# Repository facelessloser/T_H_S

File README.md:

# T_H_S

https://facelesstech.files.wordpress.com/2015/07/main_ths2.jpg

Low cost open source heart rate and body temperature monitor

Blog post can be found here

https://facelesstech.wordpress.com/2015/07/31/temp_heart_sensor/

Hackaday.io post can be found here 

https://hackaday.io/project/4910-ths

Video can be found here 

https://youtu.be/P-qDKN8uHOM

https://www.youtube.com/watch?v=heoFKFPPkZ0

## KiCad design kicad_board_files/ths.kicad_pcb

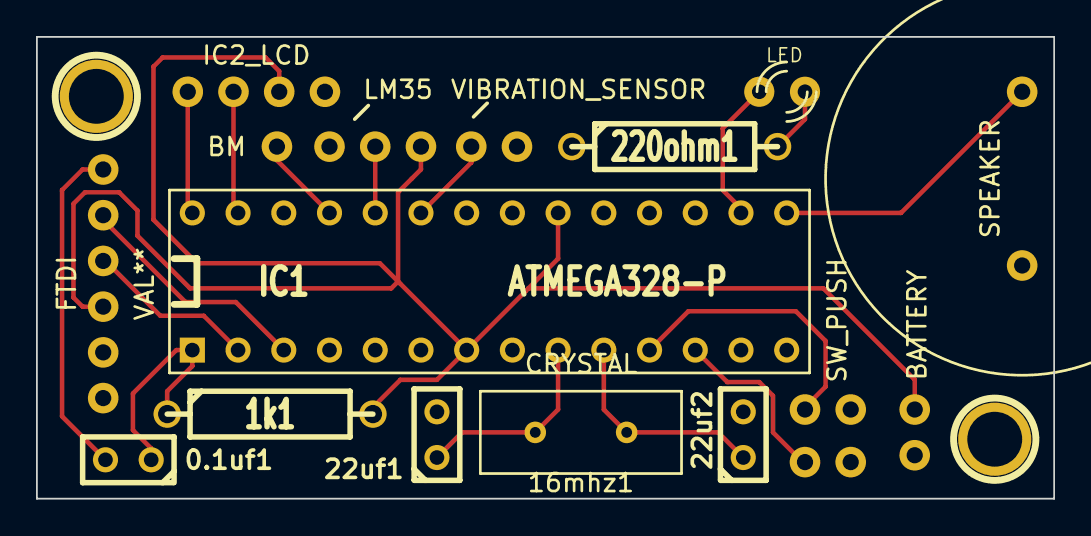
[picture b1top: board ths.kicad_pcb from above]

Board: 2 copper layers, 56.5 x 25.7 mm, 20 parts (0 on the bottom side), 15 nets.

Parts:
0.1uf1, 22uf1, 22uf2: C; C1
1PIN, 1PIN#2: P***; 1pin
1k1, 220ohm1: R; R4-5
16mhz1: CRYSTAL; Crystal_custom
BT1: BATTERY; battery_custom
D1: LED; LED_custom
FTDI: VAL**; FTDI
IC1: ATMEGA328-P; atmega328_socket
IC2_LCD1: IC2_LCD; LCD_I2C_Custom
SP1: SPEAKER; speaker_custom
SW1, SW2: SW_PUSH; push_button_custom
U1: LM35
U2: VIBRATION_SENSOR; vibration_sensor
U3: BM; battery_monitor
VAL: OSH_final_silks_back

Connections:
GND: 22uf1.2, 22uf2.2, 220ohm1.1, BT1.2, IC1.8, IC1.22, IC2_LCD1.1, SP1.1, SW1.1, SW2.1, U1.3, U2.1
unnamed: D1.1, IC1.16
unnamed: 220ohm1.2, D1.2
unnamed: IC1.15, SP1.2
unnamed: IC1.11, SW2.2
unnamed: IC1.23, U2.2
unnamed: IC1.25, U3.1
unnamed: IC1.12, SW1.2
unnamed: IC1.24, U1.2
unnamed: 16mhz1.1, 22uf2.1, IC1.10
unnamed: IC1.27, IC2_LCD1.3
unnamed: IC1.28, IC2_LCD1.4
unnamed: 16mhz1.2, 22uf1.1, IC1.9
unnamed: 0.1uf1.1, 1k1.1, IC1.1
VCC: 1k1.2, BT1.1, IC1.7, IC1.20, IC2_LCD1.2, U1.1

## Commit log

2015-04-16 Work in progess but thought I might as well get it up on here
2015-04-18 added battery percentage
2015-04-18 added battery icon
2015-04-18 cleaned up code and added comments
2015-04-19 current 19/4/15 breadboard layout
2015-04-20 added a button just because
2015-04-21 added the vcc from the battery booster to the switch
2015-05-04 added a second button but doesnt do anything yet
2015-05-09 added toggle button between f and c for the temp on the display
2015-05-11 addded serial out for temp and heart beat but really rough for now
2015-05-12 Fixed the disappearing BPM when switching between c and f on the temp. Still need to fix the battery status but that can wait
2015-05-13 Fixed that battery icon issus and cleaned up some of the start up code for the splash screen
2015-05-16 Fixed the button to toggle between led and sound for the heart beat
2015-05-23 Displays temp_c at the moment using pygame for the gui
2015-05-23 Added serial output for the python gui side
2015-05-30 changed the name of folder
2015-05-30 changed name
2015-05-31 Added a new switch and some diodes into the design
2015-06-24 long awaited update, fixed some bugs and added features
2015-07-08 Fixed the gurber files so the FTDI and speaker holes are bigger
2015-07-22 Temp and heart displayed on the currect lines on LCD
2015-07-24 changed some variables names
2015-07-31 Added links for blog and videos
2015-07-31 schematics
2015-07-31 added picture
2015-09-10 added another youtube video
2016-09-24 Added board files
